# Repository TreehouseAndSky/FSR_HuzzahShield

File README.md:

# FSR_HuzzahShield

The goal of the project is to analyze a persons sitting posture over time & give immediate feedback if the user has been sitting too long, or has adapted a bad sitting position.

To do this we connect a 4x4 Force Sensitive Resistor matrix to an ESP8266 in order to read out and and wirelessly transmit the resistance values over WiFi with the MQTT protocol.

## Sensor Hardware
Contains the eagle files of the project.

## Sensor Software
Firmware to read out the matrix. The ESP8266 is programmed using Arduino for fast prototyping & access to convenient libraries (eg the PubSubClient MQTT library). And because getting the Espressif Toolchain set up has proved to be a real pain. The data is transferred over MQTT to a central broker (I'm using an old Raspberry Pi) where data processing takes place. Which brings us to

## Broker Software
Contains the data processing code on the central hub. Work in progress.
To set up a Raspberry Pi as a MQTT broker, [this](https://www.youtube.com/watch?v=AsDHEDbyLfg) is a great video.

This README was created using [Dillinger](www.dillinger.io).

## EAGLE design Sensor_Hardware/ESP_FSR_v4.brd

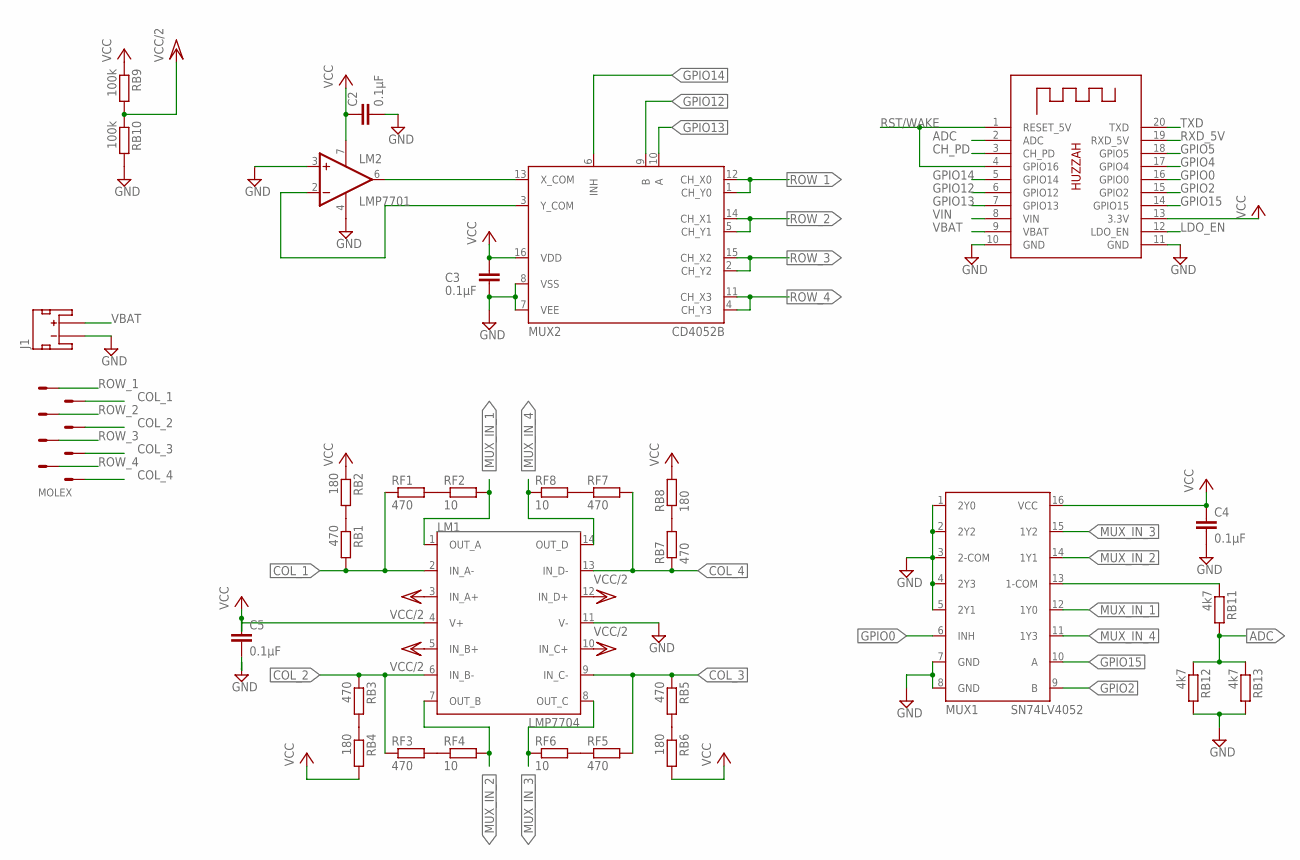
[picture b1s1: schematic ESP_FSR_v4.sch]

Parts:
C2, C3, C4, C5: 0.1µF; C0805
J1: JST_2MM_MALE; JST-2-SMD
LM1: LMP7704; D_R-PDSO-G14
LM2: LMP7701; D_R-PDSO-G08
MOLEX: 90130-3308
MUX1: SN74LV4052; D_R-PDSO-G16
MUX2: CD4052B; D_R-PDSO-G16
RB1, RB3, RB5, RB7: 470; R0805
RB2, RB4, RB6, RB8: 180; R0805
RB9, RB10: 100k; R0805
RB11, RB12, RB13: 4k7; R0805
RF1, RF3, RF5, RF7: 470; R0805
RF2, RF4, RF6, RF8: 10; R0805
U$1: HUZZAH

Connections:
ADC: RB11.2, RB12.1, RB13.1, U$1.2 (ADC)
CH_PD: U$1.3 (CH_PD)
COL_1: LM1.2 (IN_A-), MOLEX.P$2, RB1.2, RF1.1
COL_2: LM1.6 (IN_B-), MOLEX.P$4, RB3.1, RF3.1
COL_3: LM1.9 (IN_C-), MOLEX.P$6, RB5.1, RF5.2
COL_4: LM1.13 (IN_D-), MOLEX.P$8, RB7.1, RF7.2
GND: C2.2, C3.2, C4.2, C5.2, J1.1 (-), LM1.11 (V-), LM2.3 (+IN), LM2.4 (V-), MUX1.1 (2Y0), MUX1.2 (2Y2), MUX1.3 (2-COM), MUX1.4 (2Y3), MUX1.5 (2Y1), MUX1.7 (GND), MUX1.8 (GND), MUX2.7 (VEE), MUX2.8 (VSS), RB10.2, RB12.2, RB13.2, U$1.10 (GND), U$1.11 (GND)
GPIO0: MUX1.6 (INH), U$1.16 (GPIO0)
GPIO2: MUX1.9 (B), U$1.15 (GPIO2)
GPIO4: U$1.17 (GPIO4)
GPIO5: U$1.18 (GPIO5)
GPIO12: MUX2.9 (B), U$1.6 (GPIO12)
GPIO13: MUX2.10 (A), U$1.7 (GPIO13)
GPIO14: MUX2.6 (INH), U$1.5 (GPIO14)
GPIO15: MUX1.10 (A), U$1.14 (GPIO15)
LDO_EN: U$1.12 (LDO_EN)
MUX_IN_1: LM1.1 (OUT_A), MUX1.12 (1Y0), RF2.2
MUX_IN_2: LM1.7 (OUT_B), MUX1.14 (1Y1), RF4.2
MUX_IN_3: LM1.8 (OUT_C), MUX1.15 (1Y2), RF6.1
MUX_IN_4: LM1.14 (OUT_D), MUX1.11 (1Y3), RF8.1
unnamed: RB3.2, RB4.1
unnamed: RF1.2, RF2.1
unnamed: MUX1.13 (1-COM), RB11.1
unnamed: RF5.1, RF6.2
unnamed: LM2.6 (OUT), MUX2.13 (X_COM)
unnamed: LM2.2 (-IN), MUX2.3 (Y_COM)
unnamed: RF7.1, RF8.2
unnamed: RB5.2, RB6.1
unnamed: RB1.1, RB2.2
unnamed: RF3.2, RF4.1
unnamed: RB7.2, RB8.1
ROW_1: MOLEX.P$1, MUX2.1 (CH_Y0), MUX2.12 (CH_X0)
ROW_2: MOLEX.P$3, MUX2.5 (CH_Y1), MUX2.14 (CH_X1)
ROW_3: MOLEX.P$5, MUX2.2 (CH_Y2), MUX2.15 (CH_X2)
ROW_4: MOLEX.P$7, MUX2.4 (CH_Y3), MUX2.11 (CH_X3)
RST/WAKE: U$1.1 (RESET_5V), U$1.4 (GPIO16)
RXD_5V: U$1.19 (RXD_5V)
TXD: U$1.20 (TXD)
VBAT: J1.2 (+), U$1.9 (VBAT)
VCC: C2.1, C3.1, C4.1, C5.1, LM1.4 (V+), LM2.7 (V+), MUX1.16 (VCC), MUX2.16 (VDD), RB2.1, RB4.2, RB6.2, RB8.2, RB9.1, U$1.13 (3.3V)
VCC/2: LM1.3 (IN_A+), LM1.5 (IN_B+), LM1.10 (IN_C+), LM1.12 (IN_D+), RB9.2, RB10.1
VIN: U$1.8 (VIN)

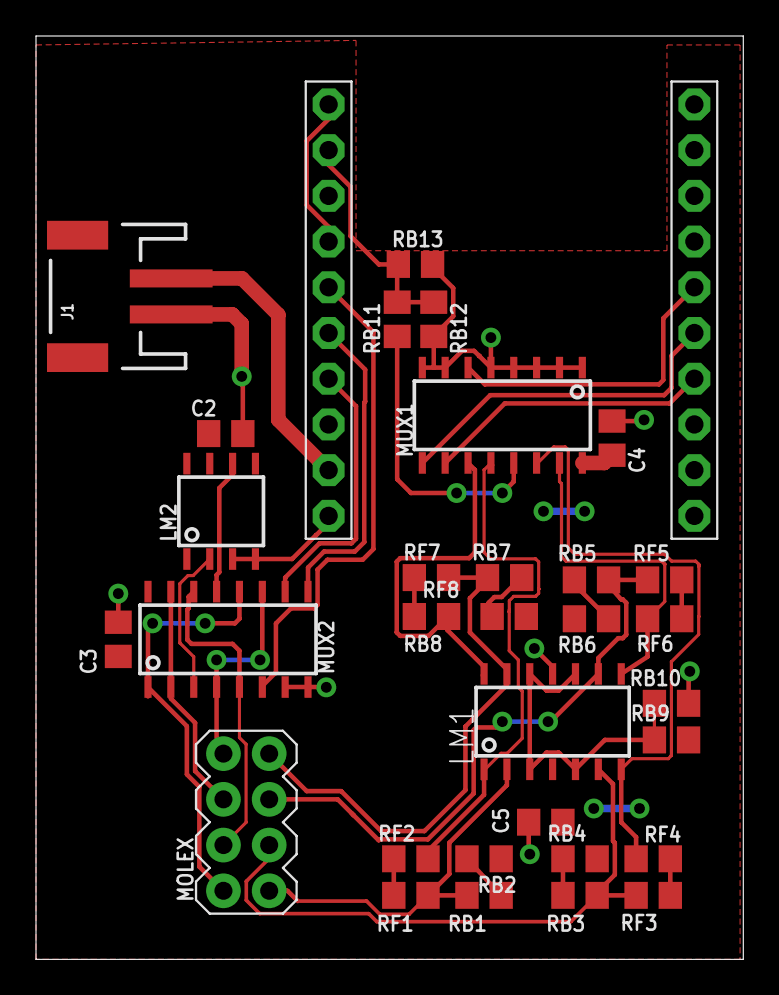
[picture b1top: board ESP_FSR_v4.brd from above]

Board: 2 copper layers, 39.3 x 51.3 mm, 32 parts (0 on the bottom side), 35 nets.

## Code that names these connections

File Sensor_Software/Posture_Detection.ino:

/*
 * Code to run on the ESP8266 posture detection
 * 
 * Requirements
 * 
 * Setup network (Wifi & MQTT)
 * 
 * Switch ROW AMPLIFIERS
 * 
 *    A   - GPIO13
 *    B   - GPIO12
 *    INH - GPIO14
 *    
 *    B   A   INH   OUT
 *    0   0   0     ROW1
 *    0   1   0     ROW2
 *    1   0   0     ROW3
 *    1   1   0     ROW4
 *    X   X   1     NONE
 *-----------------------------------------    
 *
 * Switch ADC MUX
 * 
 *    A   - GPIO15
 *    B   - GPIO2
 *    INH - GPIO0
 *    
 *    B   A   INH   OUT
 *    0   0   0     COLUMN1
 *    0   1   0     COLUMN2
 *    1   0   0     COLUMN3
 *    1   1   0     COLUMN4
 *    X   X   1     NONE
 *-----------------------------------------
 *    
 * Read ADC value
 * 
 * Analyze/(Running) Average result
 * 
 * Loop all sensor points
 * 
 * Transmit
 * 
 * Sleep
 * 
 * 
 */

#include <ESP8266WiFi.h>
#include <PubSubClient.h>
#define DEBUG 1

// Network specific values

const char* ssid = "Telenet_L&K";
const char* password = "Kikikiki01";
const char* mqtt_server = "192.168.0.177";

WiFiClient espClient;
PubSubClient client(espClient);
long lastMsg = 0;
int value = 0;
char* outTopic = "dev/test";
char *inTopic = "inTopic";

const int ROW_APin = 13;
const int ROW_BPin = 12;
const int ROW_INHPin = 14;
const int COL_APin = 15;
const int COL_BPin = 2;
const int COL_INHPin = 0;

int matrix[3][3];

void setup_wifi() {

  delay(10);
  // We start by connecting to a WiFi network
  Serial.println();
  Serial.print("Connecting to ");
  Serial.println(ssid);

  WiFi.begin(ssid, password);

  while (WiFi.status() != WL_CONNECTED) {
    delay(500);
    Serial.print(".");
  }

  randomSeed(micros());

  Serial.println("");
  Serial.println("WiFi connected");
  Serial.println("IP address: ");
  Serial.println(WiFi.localIP());
}



/*
 * Callback function for the MQTT library, this function
 * gets called when a message is published in a topic we subscribed to
 */
void callback(char* topic, byte* payload, unsigned int length) {
  Serial.print("Message arrived [");
  Serial.print(topic);
  Serial.print("] ");
  for (int i = 0; i < length; i++) {
    Serial.print((char)payload[i]);
  }
  Serial.println();

  // Switch on the LED if an 1 was received as first character
  if ((char)payload[0] == '1') {
    digitalWrite(BUILTIN_LED, LOW);   // Turn the LED on (Note that LOW is the voltage level
    // but actually the LED is on; this is because
    // it is acive low on the ESP-01)
  } else {
    digitalWrite(BUILTIN_LED, HIGH);  // Turn the LED off by making the voltage HIGH
  }

}
/*
 * Wifi connection function
 */
void reconnect() {
  // Loop until we're reconnected
  while (!client.connected()) {
    Serial.print("Attempting MQTT connection...");
    // Create a random client ID
    String clientId = "ESP8266Client-";
    clientId += String(random(0xffff), HEX);
    // Attempt to connect
    if (client.connect(clientId.c_str())) {
      Serial.println("connected");
      // Once connected, publish an announcement...
      client.publish(outTopic, "hello world");
      // ... and resubscribe
      client.subscribe(inTopic);
    } else {
      Serial.print("failed, rc=");
      Serial.print(client.state());
      Serial.println(" try again in 5 seconds");
      // Wait 5 seconds before retrying
      delay(5000);
    }
  }
}

/*
 * Switch the row we're measuring on. This drives the row MUX (CD
 */
void switch_row(int row) {
  switch (row) {
    case 0 :
      digitalWrite(ROW_APin, LOW);
      digitalWrite(ROW_BPin, LOW);
      digitalWrite(ROW_INHPin, HIGH);
      break;
      
    case 1 :
      digitalWrite(ROW_APin, LOW);
      digitalWrite(ROW_BPin, LOW);
      digitalWrite(ROW_INHPin, LOW);
      break;
      
    case 2 :
      digitalWrite(ROW_APin, HIGH);
      digitalWrite(ROW_BPin, LOW);
      digitalWrite(ROW_INHPin, LOW);
      break;
      
    case 3 :
      digitalWrite(ROW_APin, LOW);
      digitalWrite(ROW_BPin, HIGH);
      digitalWrite(ROW_INHPin, LOW);
      break;
      
    case 4 :
      digitalWrite(ROW_APin, HIGH);
      digitalWrite(ROW_BPin, HIGH);
      digitalWrite(ROW_INHPin, LOW);
      break;

    default :
      digitalWrite(ROW_APin, LOW);
      digitalWrite(ROW_BPin, LOW);
      digitalWrite(ROW_INHPin, HIGH);
      break;
  }
  
}

void switch_column(int column) {
  switch (column) {
    case 0 :
      digitalWrite(COL_APin, LOW);
      digitalWrite(COL_BPin, LOW);
      digitalWrite(COL_INHPin, HIGH);
      break;
      
    case 1 :
      digitalWrite(COL_APin, LOW);
      digitalWrite(COL_BPin, LOW);
      digitalWrite(COL_INHPin, LOW);
      break;
      
    case 2 :
      digitalWrite(COL_APin, HIGH);
      digitalWrite(COL_BPin, LOW);
      digitalWrite(COL_INHPin, LOW);
      break;
      
    case 3 :
      digitalWrite(COL_APin, LOW);
      digitalWrite(COL_BPin, HIGH);
      digitalWrite(COL_INHPin, LOW);
      break;
      
    case 4 :
      digitalWrite(COL_APin, HIGH);
      digitalWrite(COL_BPin, HIGH);
      digitalWrite(COL_INHPin, LOW);
      break;

    default :
      digitalWrite(COL_APin, LOW);
      digitalWrite(COL_BPin, LOW);
      digitalWrite(COL_INHPin, HIGH);
      break;
  }
  
}

void readPoints() {
  int sensorvalue;
  
  for(int i=0; i<=3; i++) //total delay = 4.(4.(10+4.1)) ms = 64.4ms = 256ms
  {
    switch_row(i);
    for(int j=0; j<=3; j++)
    {
      switch_column(j);
      delay(10); //todo: test settling time;
      sensorvalue = 0;

      //Take an average of 5 analog reads
      for(int k=0; k<5; k++)
      {
        #ifdef DEBUG
        sensorvalue += random(0,1025);
        #else
        sensorvalue += analogRead(A0);
        #endif;
        delay(1);
      };
      
      sensorvalue = sensorvalue/5;
      matrix[i][j] = sensorvalue;
      Serial.print("Element ");
      Serial.print(i);
      Serial.print("x");
      Serial.print(j);
      Serial.print(": ");
      Serial.println(sensorvalue);
    };
  };
  Serial.println("Readout complete");
}

void sendPoints(){
  Serial.println("Sending pressure matrix");
  
//	 Prepare a JSON payload string of format
//	{
//	    "row0":[1001,1002,1003,1004],
//	    "row1":[1005,1006,1007,1008],
//	    "row2":[1009,1010,1011,1012],
//	    "row3":[1013,1014,1015,1016]
//	}
  String payload = "{";
  for(int i=0; i<=3; i++){
      payload += "\"row";
      payload += String(i);
	  payload += "\":[";
      for(int j=0; j<=3; j++){
        payload += String(matrix[i][j]);
        if(j != 3)
          payload += ",";
      };
      payload += "]";
      if (i != 3)
        payload += ",";
  };
  payload += "}";
  
  // Send payload
  char attributes[200];
  payload.toCharArray(attributes, 200);
  client.publish(outTopic, attributes);
  Serial.println(attributes);
}

void setup() {
  pinMode(ROW_APin, OUTPUT);
  pinMode(ROW_BPin, OUTPUT);
  pinMode(ROW_INHPin, OUTPUT);
  pinMode(COL_APin, OUTPUT);
  pinMode(COL_BPin, OUTPUT);
  pinMode(COL_INHPin, OUTPUT);
  switch_row(0);
  switch_column(0);
  pinMode(BUILTIN_LED, OUTPUT);     // Initialize the BUILTIN_LED pin as an output
  Serial.begin(115200);
  setup_wifi();
  client.setServer(mqtt_server, 1883);
  client.setCallback(callback);
}

void loop() {
  
  if (!client.connected()) {
    reconnect();
  }
  client.loop();

  //turn off wifi
  readPoints();

  long now = millis();
  if (now - lastMsg > 5000) {
    //turn on wifi
    lastMsg = now;
    ++value;
    sendPoints();
  }
}

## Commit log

2017-06-09 added Eagle files to the Hardware folder
2017-06-09 Adding some directories
2017-06-09 finalizing, I hope
2017-06-09 renaming folder
2017-06-09 update the readme
2017-06-12 lock files?
2017-06-12 rm lock files
2017-06-12 Going Arduino
2017-06-24 Adding a few iterations & a to do list
2017-06-24 Added code to send pressure data over MQTT using JSON syntax
2017-06-24 updated the README
2017-06-27 Typo correction
2017-06-27 initial broker software commit
2017-06-27 Change name
2017-06-27 setting up & testing branch
2017-06-27 testing complete & branch working. Learning is fun
2017-06-27 datahandler example & software README
2017-06-27 testing & setting up datahandler.py, a python MQTT client that decodes incoming JSON packets
2017-06-28 Reading in JSON with python works on mac, prepared everything for testing on rpi
2017-06-28 Update the JSON format the sensor sends

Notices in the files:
parts and their libraries:
SparkFun-Connectors: Licensing: Creative Commons ShareAlike 4.0 International - https://creativecommons.org/licenses/by-sa/4.0
